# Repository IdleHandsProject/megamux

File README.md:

# MegaMUX
A 32 Channel Multiplexer Breakout Board.

Order the board here - https://www.pcbway.com/project/shareproject/MegaMUX___32_Channel_Multiplexer_Breakout.html

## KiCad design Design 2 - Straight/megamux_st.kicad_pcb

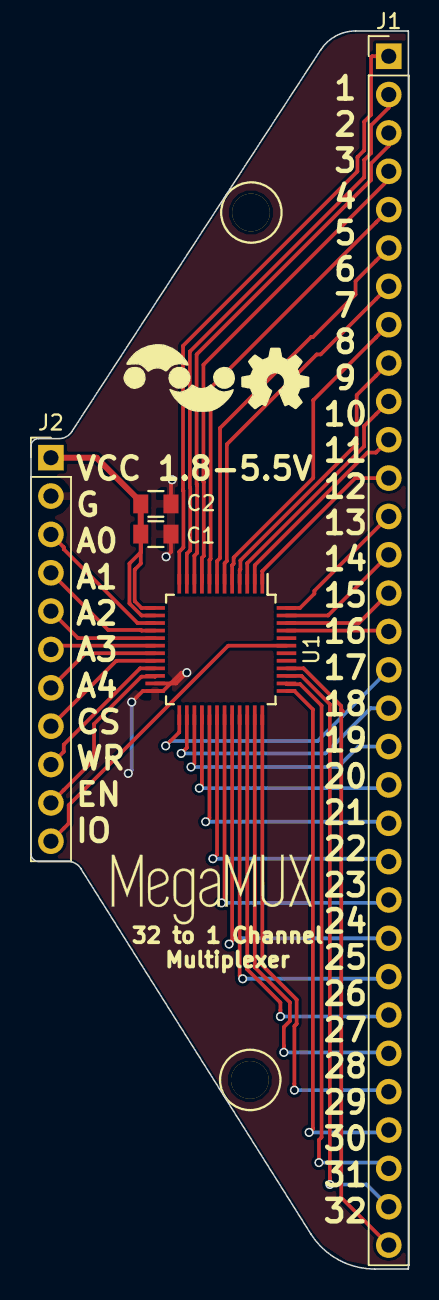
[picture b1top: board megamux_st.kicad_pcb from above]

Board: 2 copper layers, 25.0 x 82.0 mm, 5 parts (0 on the bottom side), 43 nets.

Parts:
C1: 0.1uF; C_0805
C2: 1uF; C_0805
J1: Conn_01x32; Pin_Header_Straight_1x32_Pitch2.54mm
J2: Conn_01x11; Pin_Header_Straight_1x11_Pitch2.54mm
U1: ADG732; TQFP-48_7x7mm_Pitch0.5mm

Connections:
A0: J2.3, U1.15
A1: J2.4, U1.16
A2: J2.5, U1.17
A3: J2.6, U1.18
A4: J2.7, U1.19
CS: J2.8, U1.20
EN: J2.10, U1.22
GND: C1.2, C2.2, J2.2, U1.23, U1.24
IO: J2.11, U1.43
unnamed: J1.1, U1.12
unnamed: J1.2, U1.11
unnamed: J1.3, U1.10
unnamed: J1.4, U1.9
unnamed: J1.5, U1.8
unnamed: J1.6, U1.7
unnamed: J1.7, U1.6
unnamed: J1.8, U1.5
unnamed: J1.9, U1.4
unnamed: J1.10, U1.3
unnamed: J1.11, U1.2
unnamed: J1.12, U1.1
unnamed: J1.13, U1.48
unnamed: J1.14, U1.47
unnamed: J1.15, U1.46
unnamed: J1.16, U1.45
unnamed: J1.17, U1.25
unnamed: J1.18, U1.26
unnamed: J1.19, U1.27
unnamed: J1.20, U1.28
unnamed: J1.21, U1.29
unnamed: J1.22, U1.30
unnamed: J1.23, U1.31
unnamed: J1.24, U1.32
unnamed: J1.25, U1.33
unnamed: J1.26, U1.34
unnamed: J1.27, U1.35
unnamed: J1.28, U1.36
unnamed: J1.29, U1.37
unnamed: J1.30, U1.38
unnamed: J1.31, U1.39
unnamed: J1.32, U1.40
VCC: C1.1, C2.1, J2.1, U1.13, U1.14
WR: J2.9, U1.21

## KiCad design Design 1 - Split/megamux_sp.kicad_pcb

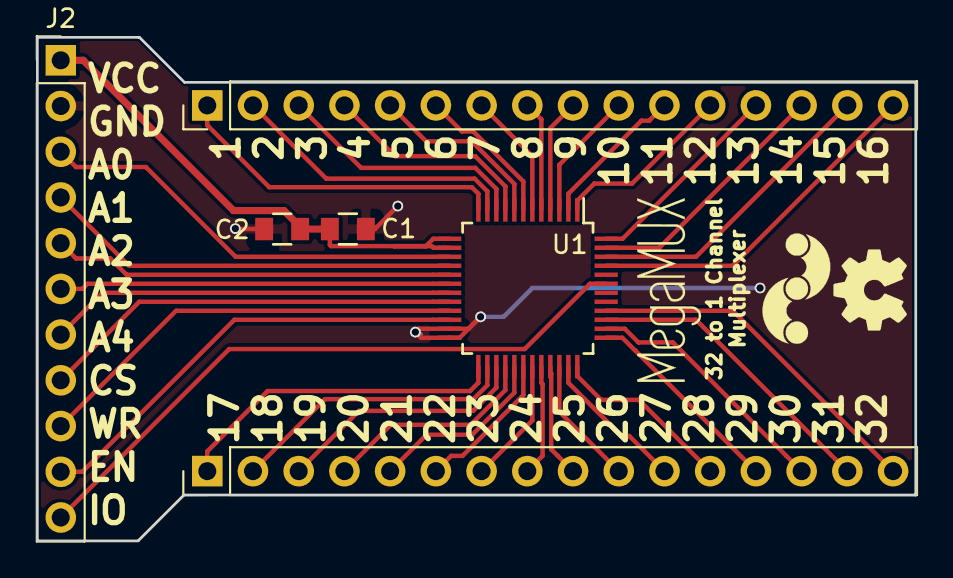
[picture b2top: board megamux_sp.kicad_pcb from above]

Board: 2 copper layers, 48.8 x 28.0 mm, 7 parts (0 on the bottom side), 43 nets.

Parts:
C1: 0.1uF; C_0805
C2: 1uF; C_0805
J2: Conn_01x11; Pin_Header_Straight_1x11_Pitch2.54mm
OSHW: LOGO; OSHLogo
P1, P2: CONN_01X16; Pin_Header_Straight_1x16_Pitch2.54mm
U1: ADG732; TQFP-48_7x7mm_Pitch0.5mm

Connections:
A0: J2.3, U1.15
A1: J2.4, U1.16
A2: J2.5, U1.17
A3: J2.6, U1.18
A4: J2.7, U1.19
CS: J2.8, U1.20
EN: J2.10, U1.22
GND: C1.2, C2.2, J2.2, U1.23, U1.24
IO: J2.11, U1.43
unnamed: P1.1, U1.12
unnamed: P1.2, U1.11
unnamed: P1.3, U1.10
unnamed: P1.4, U1.9
unnamed: P1.5, U1.8
unnamed: P1.6, U1.7
unnamed: P1.7, U1.6
unnamed: P1.8, U1.5
unnamed: P1.9, U1.4
unnamed: P1.10, U1.3
unnamed: P1.11, U1.2
unnamed: P1.12, U1.1
unnamed: P1.13, U1.48
unnamed: P1.14, U1.47
unnamed: P1.15, U1.46
unnamed: P1.16, U1.45
unnamed: P2.1, U1.25
unnamed: P2.2, U1.26
unnamed: P2.3, U1.27
unnamed: P2.4, U1.28
unnamed: P2.5, U1.29
unnamed: P2.6, U1.30
unnamed: P2.7, U1.31
unnamed: P2.8, U1.32
unnamed: P2.9, U1.33
unnamed: P2.10, U1.34
unnamed: P2.11, U1.35
unnamed: P2.12, U1.36
unnamed: P2.13, U1.37
unnamed: P2.14, U1.38
unnamed: P2.15, U1.39
unnamed: P2.16, U1.40
VCC: C1.1, C2.1, J2.1, U1.13, U1.14
WR: J2.9, U1.21
